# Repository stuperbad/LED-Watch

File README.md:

# LED-Watch

A round LED wristwatch: 132 small LEDs (12 hours, 60 minutes, 60 seconds as three concentric rings) driven straight from an AVR microcontroller, with an accelerometer to wake it. Two variants share the idea and some code but have different hardware, so each lives in its own folder.

| Open this KiCad project | Variant | Status |
|---|---|---|
| [`single-color/hardware/LED Watch - Single Color.kicad_pro`](single-color/hardware/) | White LEDs, solar-charged (TI BQ25570 + one Anysolar cell + two small LiPo cells), AVR128DB48, piezo buzzer, 42 mm board | **Revision A is an order candidate** (JLCPCB quote $308.63 for 5 assembled boards), fully routed, DRC clean, **not ordered yet**. Firmware (alarm, weekday lights, sounds) and a browser simulator are in the folder. Start with [`single-color/README.md`](single-color/README.md). Tagged `rev-A`. |
| [`rgb/LED Watch - RGB.kicad_pro`](rgb/) | RGB LEDs that JLCPCB can assemble (common-anode), AVR128DB64, solar + LiPo + buzzer like the single-colour watch | **Placement sketch only** (2026-10-15): board size and fit worked out, no schematic or routing yet. Start with `rgb/docs/DESIGN-SKETCH.md`. The earlier RGB board (Harvatek LEDs, ATmega165PA, fully routed, not buildable: parts out of stock) is in `rgb/archive/2026-10-14 old RGB board ...` |

## Layout of the repository
```
LED-Watch/
  single-color/        the solar white-LED watch
    hardware/          KiCad project, custom footprints, production files (Gerbers, BOM, placement), schematic generator
    firmware/          AVR firmware (C), browser simulator, tests
    docs/              design notes, decision log, checklists, datasheets, research
    tools/             layout / routing / checking scripts
    archive/           older board generations of this variant
  rgb/                 the RGB watch
    LED Watch - RGB.*  the RGB project (placement sketch, 2026-10-15)
    docs/              DESIGN-SKETCH.md, pin plan, BOM candidates
    footprints/ data/ tools/ renders/   LED footprint, LED map, sketch generator, pictures
    mechanical/        outline drawings and the 3D print (of the old 43 mm board)
    archive/           the old routed RGB board and everything older
```
Both variants live side by side on `main`; branches are for work in progress. Revisions are git tags (`rev-A`, ...) rather than file names.
Code that both variants will share (LED matrix scan, RTC and mode state machine, accelerometer driver) can move to a top-level `shared/` folder when RGB firmware starts; `single-color/firmware/` is the starting point.

## Reviewing
Open `single-color/README.md` (what everything is), then `single-color/docs/REVIEW-GUIDE.md` (what to check first), and `single-color/docs/PRE-ORDER-CHECKLIST.md` (what is still open).

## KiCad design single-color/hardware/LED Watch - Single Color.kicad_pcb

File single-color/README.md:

# LED Watch (single color, solar)

A wrist-worn clock that tells the time with 132 tiny white LEDs on three concentric rings (12 hour, 60 minute, 60 second), seven mode LEDs that double as weekday lights,
a piezo buzzer, a motion sensor to wake it, a solar cell and two LiPo cells on the back, and no case. Run by Evan Finkle with Claude (Anthropic) doing research, scripting and layout.

**Status (2026-11-02): revision C is the current design, not ordered yet.** Revision C is revision B with charging and programming moved from four pogo pads to a **USB-C receptacle** on the back (GCT USB4110, a TI BQ21040 charger, UPDI on the two SBU pins), the solar cell pad connection fixed (on revision B the cell pad was on a differently named net and not wired to the harvester), the outer LED-column arcs pulled in from the board edge, and the silkscreen reduced to the numbers, labels and a few orientation marks. Revision B (pogo pads, code word `pogo-b`) is deprecated and archived in `archive/boards/rev-B-pogo/`; revision A in `archive/boards/rev-A-2026-10-29-pre-repin/`. Nothing has been powered up.
Requires **KiCad 10** (the project files will not open in older versions).
The checklist of what is still open is `docs/PRE-ORDER-CHECKLIST.md`; the reasoning behind every decision is `docs/DECISION-LOG.md`.

| | |
|---|---|
| Board | 42.0 mm circle with two strap lugs and 2.5 mm strap slots, 4 layers, 1.6 mm, JLCPCB rules (0.10 mm track/space, 0.15 mm vias) |
| MCU | Microchip AVR128DB48 (VQFN-48), UPDI programming through the USB-C receptacle's SBU pins (1 k in series, BAT54WS clamp); no reset pad (RESET on PF6 is not wired out) |
| Power | Anysolar KXOB25-05X3TF cell -> TI BQ25570 harvester -> 2 protected LiPo pouches (JST SH plugs); USB-C 5 V -> TI BQ21040 charger (54 mA) -> the same pouches |
| Sensor / sound | ST LIS2DW12 accelerometer (wrist raise, tap), Murata PKMCS0909E4000-R1 piezo on PB4/PB5 |
| Buttons | two, symmetric, low on the face |

## Folder map

| Folder | What is in it |
|---|---|
| **`hardware/`** | **The KiCad project. Open `hardware/LED Watch - Single Color.kicad_pro`.** `LED Watch - Single Color.kicad_sch` (schematic, hand-arranged in KiCad since 2026-10-29; `gen_schematic.py` is only a reference now and would overwrite that layout), `LED Watch - Single Color.kicad_pcb` (the routed board), `footprints/LEDWatch.pretty` (custom footprints), `netlist.xml` (exported from the schematic, read by the firmware tools) |
| `hardware/production/` | what you send to JLCPCB (revision C): `LED Watch - Single Color - gerbers.zip` (+ the loose `gerbers/`), `assembly/BOM.csv` and `CPL.csv` |
| `hardware/source/` | inputs of the layout pipeline: `layout-D-hand-placement.kicad_pcb` (the hand placement the routing started from), `nets.txt`, `crystal_exclude.txt` |
| `hardware/renders/` | top and bottom pictures of the board |
| `hardware/REVISIONS.md` | the revision table (A and B archived, **C = current**); revisions are git tags, not file names |
| `firmware/` | the watch software: `c/` AVR firmware (portable core `watch.c`, hardware layer `hw/`), `sim/` browser simulator running the same logic, `HANDOFF.md` current status. Start with `firmware/HANDOFF.md` |
| `mechanical/` | 3D-printable strap/fit test models: blank board, board with big-part stand-ins, snap-on skin-side bumper (`print/` has the STL files, `README.md` the print notes, `make_models.py` rebuilds them) |
| `docs/` | `BRING-UP.md` (first power-up: how the battery and power work, measurements, programming), `DESIGN-UX.md` (modes, buttons, LEDs, sounds), `DECISION-LOG.md`, `PRE-ORDER-CHECKLIST.md`, `SCHEMATIC-GUIDE.md`, `JLCPCB-RULES.md`, `ASSEMBLY-AND-COST.md`, `mcu-pinmaps.md`, `PIN-VERIFICATION.md` (every MCU pin checked against the datasheets, run `tools/verify_pins.py`); `datasheets/`; `research/` (solar, power, MCU studies, the power workbook) |
| `tools/` | the scripts that produced and checked the layout (routing pipeline, DRC helpers, BOM/placement export). KiCad's own Python is needed for the `pcbnew` ones |
| `archive/` | older board generations and experiments (revision A, revision B with pogo pads); see `archive/README.md` |

## Regenerating things

```
# the netlist the firmware tools read (edit the schematic in KiCad; do not re-run gen_schematic.py over it)
cd hardware
"C:\Program Files\KiCad\10.0\bin\kicad-cli.exe" sch export netlist --format kicadxml -o netlist.xml "LED Watch - Single Color.kicad_sch"

# firmware pin map and simulator face data from the schematic netlist and the board
cd ..\firmware
python gen_pins.py
"C:\Program Files\KiCad\10.0\bin\python.exe" sim\export_face_board.py

# production files from the board
cd ..\hardware
kicad-cli pcb export gerbers --subtract-soldermask --layers F.Cu,In1.Cu,In2.Cu,B.Cu,F.Mask,B.Mask,F.Silkscreen,B.Silkscreen,Edge.Cuts -o production\gerbers\ "LED Watch - Single Color.kicad_pcb"
kicad-cli pcb export drill --format excellon --excellon-separate-th --generate-map --map-format gerberx2 -o production\gerbers\ "LED Watch - Single Color.kicad_pcb"
kicad-cli pcb export pos --format csv --units mm --side both --smd-only --exclude-dnp -o production\assembly\pos_raw.csv "LED Watch - Single Color.kicad_pcb"
python ..\tools\make_bom_cpl.py production\assembly\pos_raw.csv production\assembly
```

Firmware tests (PC): `python firmware\c\test\run_diff.py` (JavaScript vs C core, frame for frame), `run_unit.py`, `run_hw.py`. AVR build: `powershell -File firmware\c\build_fw.ps1`.
Simulator: `python firmware\sim\serve.py 8765`, then open http://127.0.0.1:8765/index.html.

## How the layout was made (so the tools make sense)
Evan hand-placed the parts in KiCad (`hardware/source/layout-D-hand-placement`), then Claude's scripts in `tools/` did the symmetry tidy-up, the real footprints, the crystal ground
guard, the polar routing of the LED rings (`polar_route.py`), a grid router for the rest (`grid_route2.py`), via/stub clean-up, the ground plane (`fix_gnd_zone.py`) and the checks
(`check_pad_entry.py`, `dfm_gaps.py`, DRC). Evan then hand-edited the result in KiCad. The step by step story is in `docs/DECISION-LOG.md`.

## Related
The earlier RGB version is in `../rgb/` (never built): open `../rgb/LED Watch - RGB.kicad_pro`.

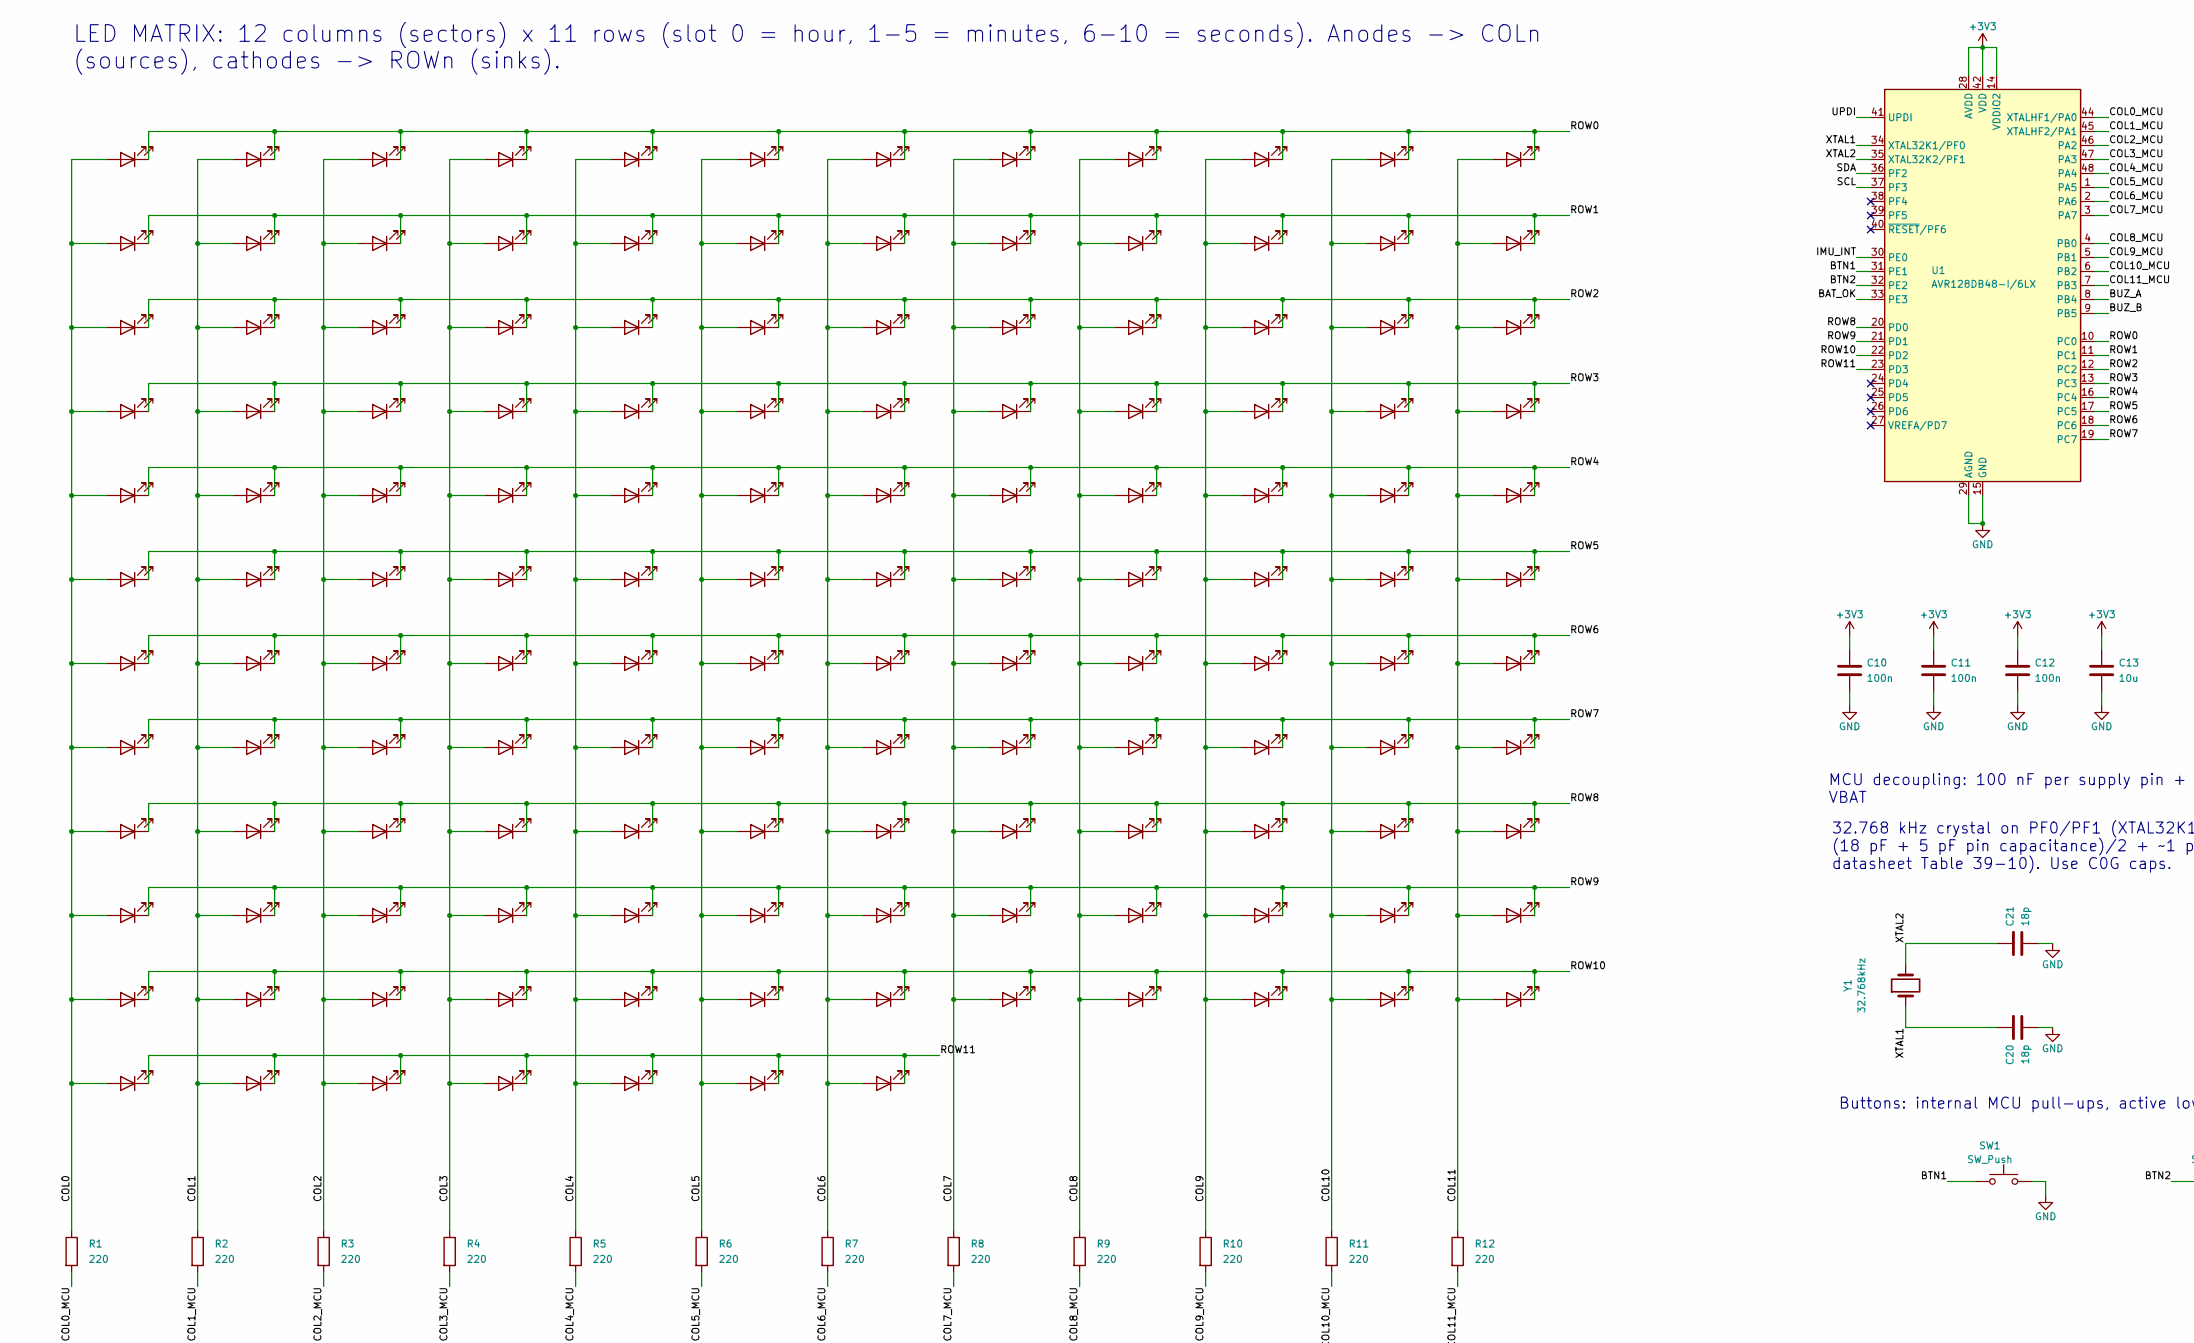
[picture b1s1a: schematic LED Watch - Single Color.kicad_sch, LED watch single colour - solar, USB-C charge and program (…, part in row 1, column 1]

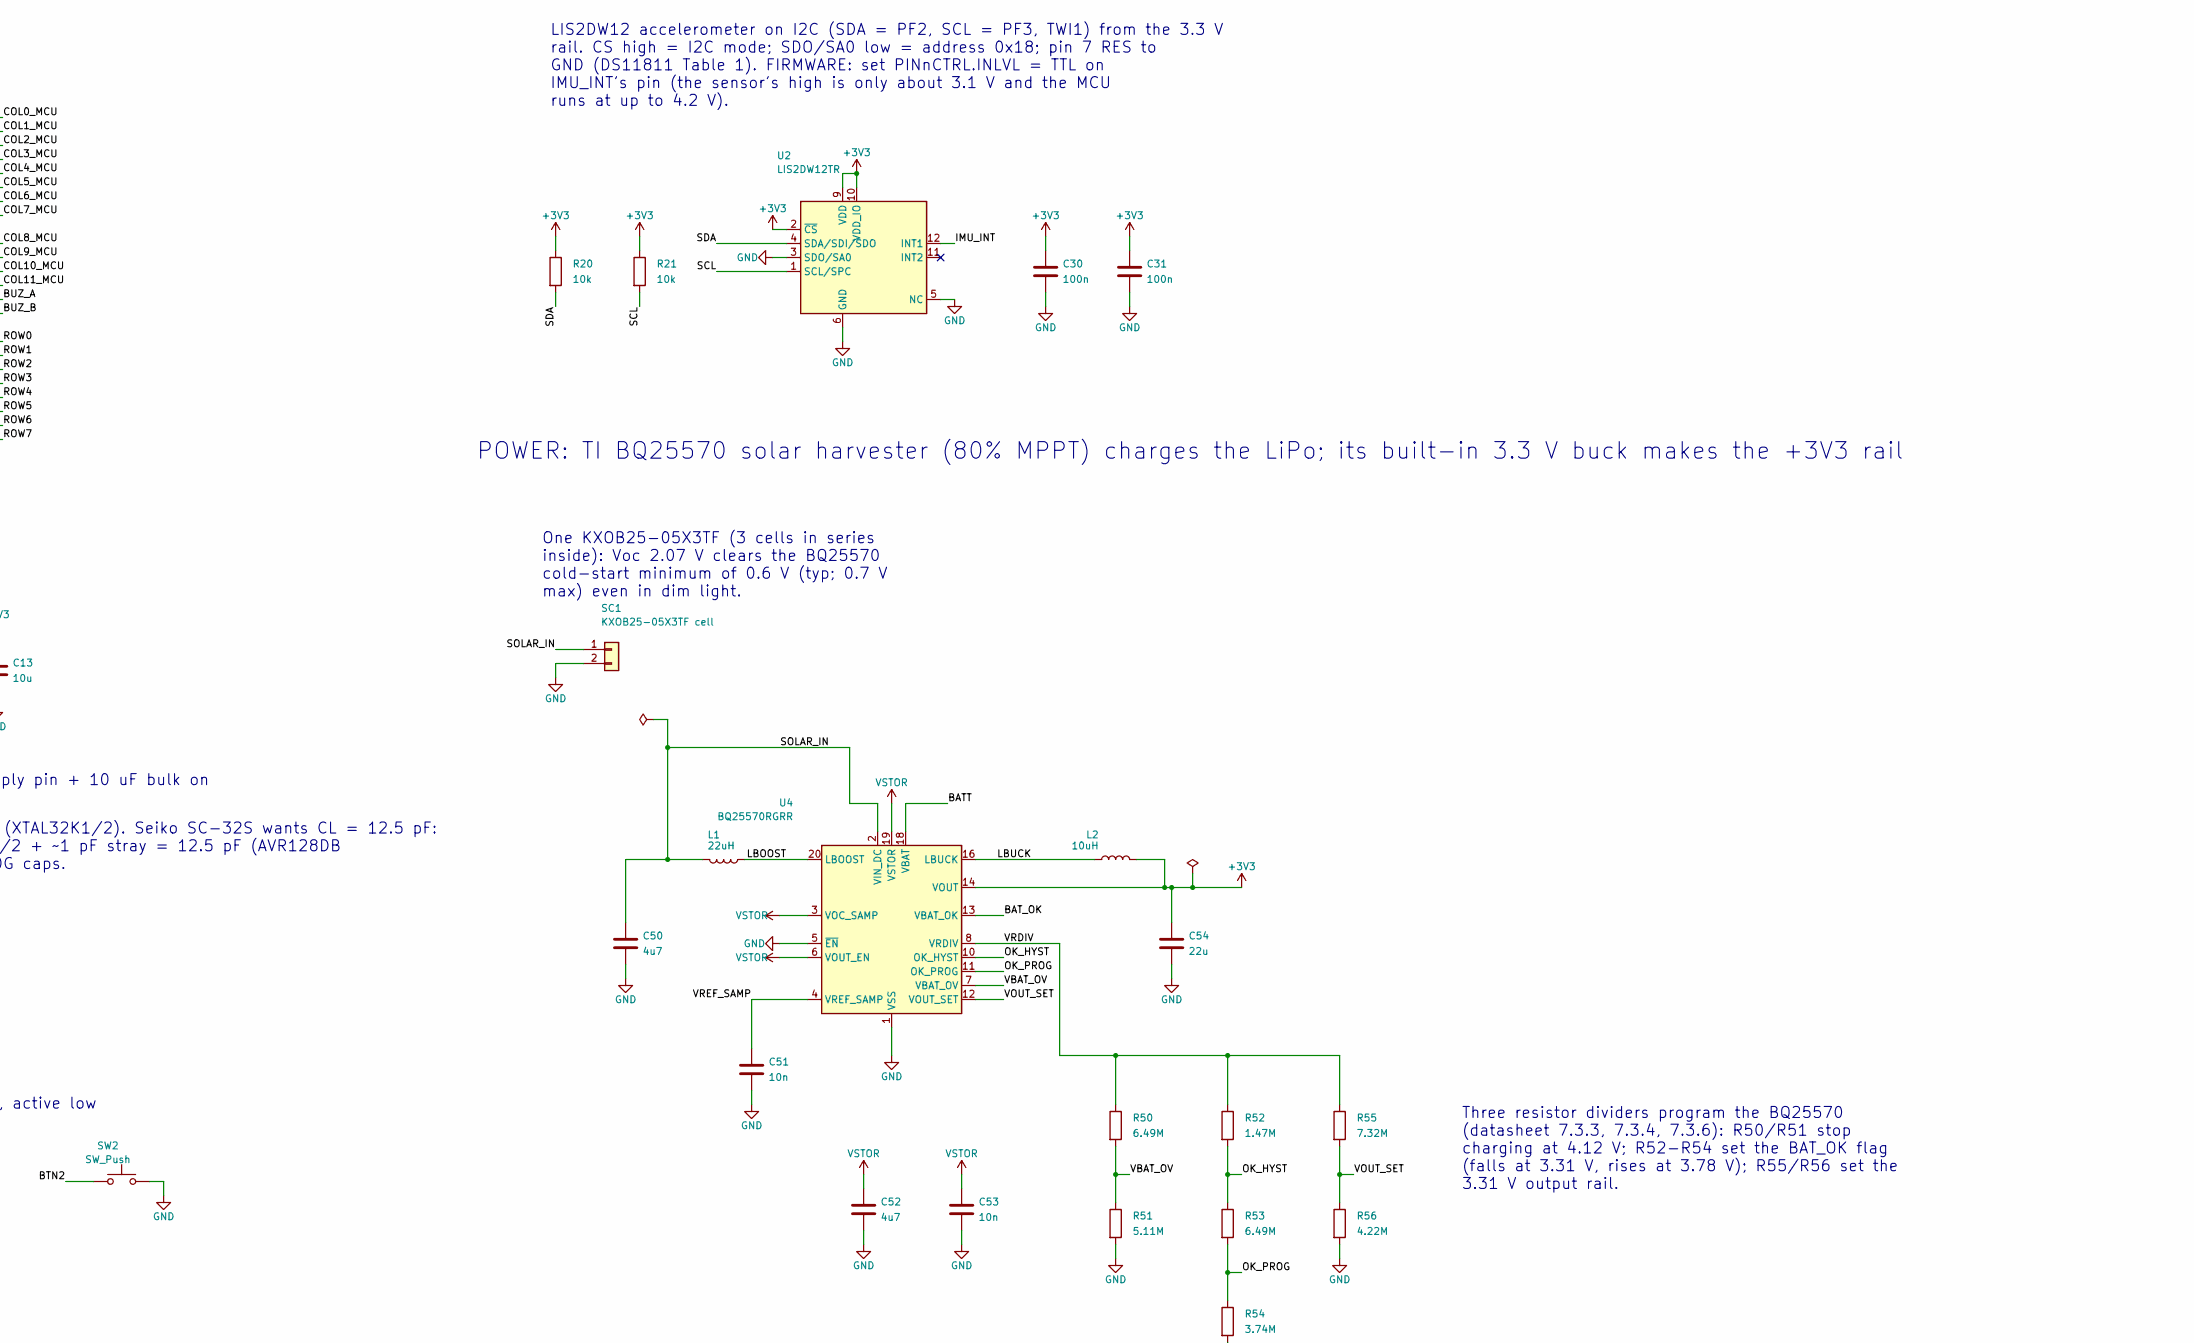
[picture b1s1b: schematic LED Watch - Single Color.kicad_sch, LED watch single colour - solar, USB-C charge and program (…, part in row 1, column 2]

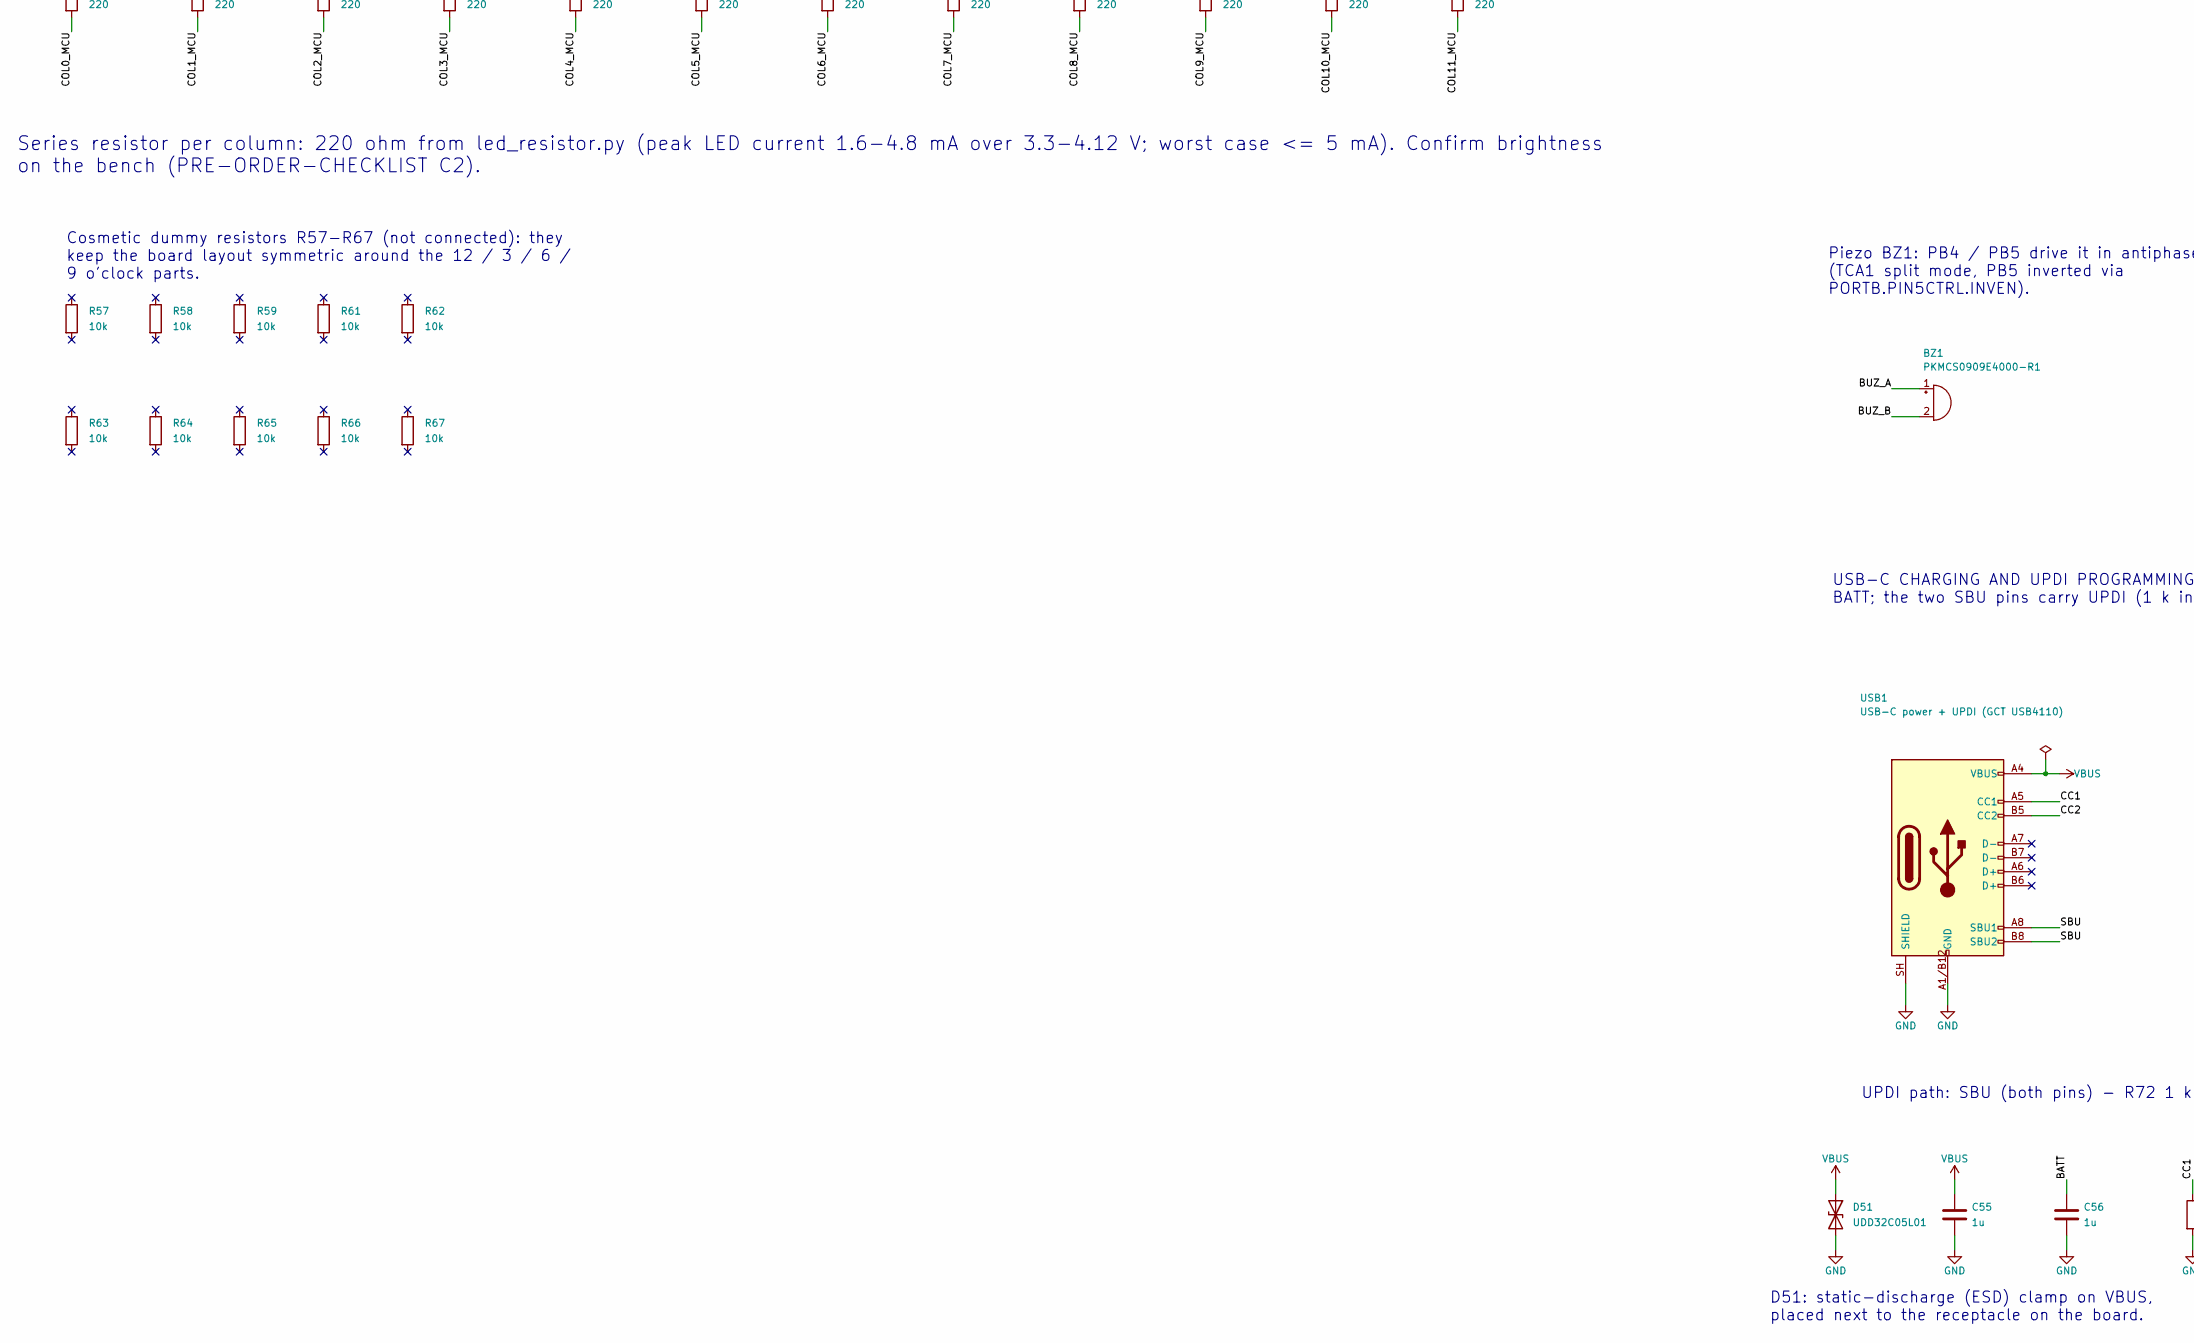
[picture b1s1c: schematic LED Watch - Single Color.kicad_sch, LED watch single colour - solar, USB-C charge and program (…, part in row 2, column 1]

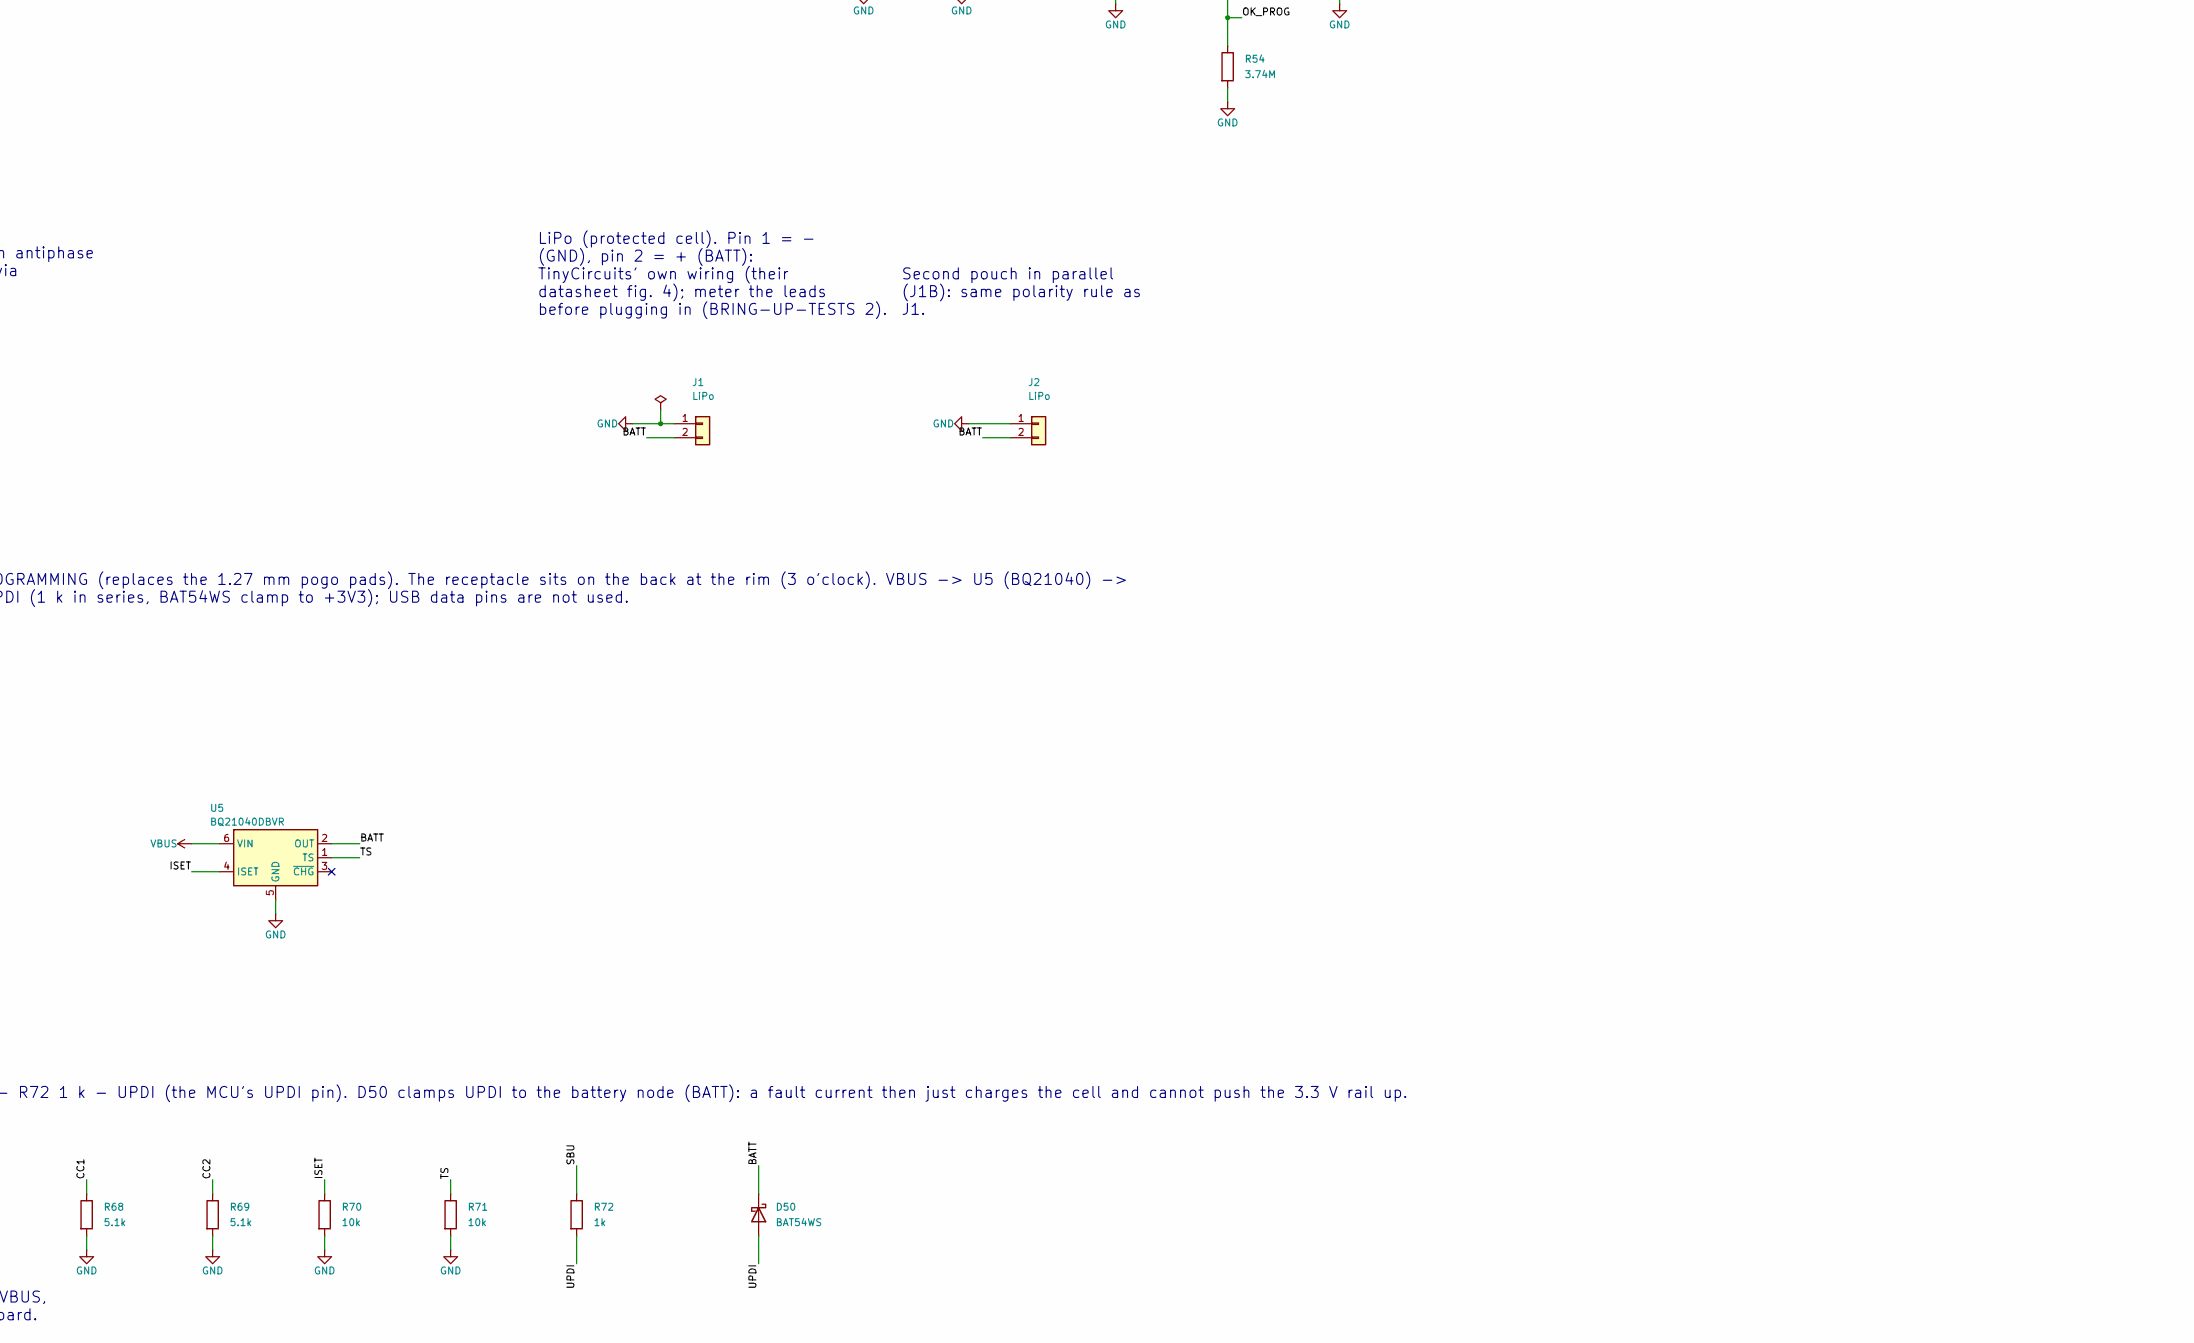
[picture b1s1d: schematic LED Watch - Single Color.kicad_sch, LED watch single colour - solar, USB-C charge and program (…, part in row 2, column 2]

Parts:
BZ1: PKMCS0909E4000-R1; Piezo_Murata_PKMCS0909E4000-R1_9x9mm; MPN PKMCS0909E4000-R1; LCSC C910763
C10, C11, C12, C30, C31: 100n; C_0402_1005Metric
C13: 10u; C_0402_1005Metric
C20, C21: 18p; C_0402_1005Metric
C50, C52: 4u7; C_0402_1005Metric
C51, C53: 10n; C_0402_1005Metric
C54: 22u; C_0805_2012Metric
C55, C56: 1u; C_0402_1005Metric; LCSC C52923
D50: BAT54WS; D_SOD-323; MPN BAT54WS; LCSC C304155
D51: UDD32C05L01; D_SOD-323; MPN UDD32C05L01; LCSC C19185929
H1, H2, H3, H4, H5, H6, H7, H8, H9, H10, H11, H12: LED white 0603; LED_0603_1608Metric
IND1: SET; LED_0402_1005Metric
IND2: TMR; LED_0402_1005Metric
IND3: BAT; LED_0402_1005Metric
IND4: FUN; LED_0402_1005Metric
IND5: CFG; LED_0402_1005Metric
IND6: LCK; LED_0402_1005Metric
IND7: ALM; LED_0402_1005Metric
J1, J2: LiPo; JST_SH_SM02B-SRSS-TB_1x02-1MP_P1.00mm_Horizontal
L1: 22uH; L_1210_3225Metric
L2: 10uH; L_1210_3225Metric
M0, M1, M2, M3, M4, M5, M6, M7, M8, M9, M10, M11, M12, M13, M14, M15, M16, M17, M18, M19, M20, M21, M22, M23, M24, M25, M26, M27, M28, M29, M30, M31, M32, M33, M34, M35, M36, M37, M38, M39, M40, M41, M42, M43, M44, M45, M46, M47, M48, M49, M50, M51, M52, M53, M54, M55, M56, M57, M58, M59: LED white 0402; LED_0402_1005Metric
R1, R2, R3, R4, R5, R6, R7, R8, R9, R10, R11, R12: 220; R_0402_1005Metric
R20, R21, R57, R58, R59, R61, R62, R63, R64, R65, R66, R67: 10k; R_0402_1005Metric
R50, R53: 6.49M; R_0402_1005Metric
R51: 5.11M; R_0402_1005Metric
R52: 1.47M; R_0402_1005Metric
R54: 3.74M; R_0402_1005Metric
R55: 7.32M; R_0402_1005Metric
R56: 4.22M; R_0402_1005Metric
R68, R69: 5.1k; R_0402_1005Metric; LCSC C25905
R70, R71: 10k; R_0402_1005Metric; LCSC C25744
R72: 1k; R_0402_1005Metric; LCSC C11702
S0, S1, S2, S3, S4, S5, S6, S7, S8, S9, S10, S11, S12, S13, S14, S15, S16, S17, S18, S19, S20, S21, S22, S23, S24, S25, S26, S27, S28, S29, S30, S31, S32, S33, S34, S35, S36, S37, S38, S39, S40, S41, S42, S43, S44, S45, S46, S47, S48, S49, S50, S51, S52, S53, S54, S55, S56, S57, S58, S59: LED white 0201; LED_0201_0603Metric
SC1: KXOB25-05X3TF cell; KXOB25_cell_2pad_23x8mm
SW1, SW2: SW_Push; SW_Push_1P1T_NO_CK_KMR2
U1: AVR128DB48-I/6LX; QFN-48-1EP_6x6mm_P0.4mm_EP4.2x4.2mm
U2: LIS2DW12TR; LGA-12_2x2mm_P0.5mm; MPN LIS2DW12TR
U4: BQ25570RGRR; BQ25570RGR_VQFN-20_3.5x3.5mm_P0.5mm_EP2.05mm
U5: BQ21040DBVR; SOT-23-6; MPN BQ21040DBVR; LCSC C202311
USB1: USB-C power + UPDI (GCT USB4110); USB_C_Receptacle_GCT_USB4110; MPN USB4110-GF-A
Y1: 32.768kHz; Crystal_SMD_3215-2Pin_3.2x1.5mm; MPN ABS07-32.768KHZ-T

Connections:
+3V3: C10.1, C11.1, C12.1, C13.1, C30.1, C31.1, C54.1, L2.2, R20.1, R21.1, U1.14 (VDDIO2), U1.28 (AVDD), U1.42 (VDD), U2.2 (~CS), U2.9 (VDD), U2.10 (VDD_IO), U4.14 (VOUT)
/BATT: C56.1, D50.1 (K), J1.2, J2.2, U4.18 (VBAT), U5.2 (OUT)
/BAT_OK: U1.33 (PE3), U4.13 (VBAT_OK)
/BTN1: SW1.1, U1.31 (PE1)
/BTN2: SW2.1, U1.32 (PE2)
/BUZ_A: BZ1.1 (+), U1.8 (PB4)
/BUZ_B: BZ1.2 (-), U1.9 (PB5)
/CC1: R68.1, USB1.A5 (CC1)
/CC2: R69.1, USB1.B5 (CC2)
/COL0: H12.2 (A), IND1.2 (A), M0.2 (A), M1.2 (A), M2.2 (A), M3.2 (A), M4.2 (A), R1.1, S0.2 (A), S1.2 (A), S2.2 (A), S3.2 (A), S4.2 (A)
/COL0_MCU: R1.2, U1.44 (XTALHF1/PA0)
/COL1: H1.2 (A), IND2.2 (A), M5.2 (A), M6.2 (A), M7.2 (A), M8.2 (A), M9.2 (A), R2.1, S5.2 (A), S6.2 (A), S7.2 (A), S8.2 (A), S9.2 (A)
/COL1_MCU: R2.2, U1.45 (XTALHF2/PA1)
/COL2: H2.2 (A), IND3.2 (A), M10.2 (A), M11.2 (A), M12.2 (A), M13.2 (A), M14.2 (A), R3.1, S10.2 (A), S11.2 (A), S12.2 (A), S13.2 (A), S14.2 (A)
/COL2_MCU: R3.2, U1.46 (PA2)
/COL3: H3.2 (A), IND4.2 (A), M15.2 (A), M16.2 (A), M17.2 (A), M18.2 (A), M19.2 (A), R4.1, S15.2 (A), S16.2 (A), S17.2 (A), S18.2 (A), S19.2 (A)
/COL3_MCU: R4.2, U1.47 (PA3)
/COL4: H4.2 (A), IND5.2 (A), M20.2 (A), M21.2 (A), M22.2 (A), M23.2 (A), M24.2 (A), R5.1, S20.2 (A), S21.2 (A), S22.2 (A), S23.2 (A), S24.2 (A)
/COL4_MCU: R5.2, U1.48 (PA4)
/COL5: H5.2 (A), IND6.2 (A), M25.2 (A), M26.2 (A), M27.2 (A), M28.2 (A), M29.2 (A), R6.1, S25.2 (A), S26.2 (A), S27.2 (A), S28.2 (A), S29.2 (A)
/COL5_MCU: R6.2, U1.1 (PA5)
/COL6: H6.2 (A), IND7.2 (A), M30.2 (A), M31.2 (A), M32.2 (A), M33.2 (A), M34.2 (A), R7.1, S30.2 (A), S31.2 (A), S32.2 (A), S33.2 (A), S34.2 (A)
/COL6_MCU: R7.2, U1.2 (PA6)
/COL7: H7.2 (A), M35.2 (A), M36.2 (A), M37.2 (A), M38.2 (A), M39.2 (A), R8.1, S35.2 (A), S36.2 (A), S37.2 (A), S38.2 (A), S39.2 (A)
/COL7_MCU: R8.2, U1.3 (PA7)
/COL8: H8.2 (A), M40.2 (A), M41.2 (A), M42.2 (A), M43.2 (A), M44.2 (A), R9.1, S40.2 (A), S41.2 (A), S42.2 (A), S43.2 (A), S44.2 (A)
/COL8_MCU: R9.2, U1.4 (PB0)
/COL9: H9.2 (A), M45.2 (A), M46.2 (A), M47.2 (A), M48.2 (A), M49.2 (A), R10.1, S45.2 (A), S46.2 (A), S47.2 (A), S48.2 (A), S49.2 (A)
/COL9_MCU: R10.2, U1.5 (PB1)
/COL10: H10.2 (A), M50.2 (A), M51.2 (A), M52.2 (A), M53.2 (A), M54.2 (A), R11.1, S50.2 (A), S51.2 (A), S52.2 (A), S53.2 (A), S54.2 (A)
/COL10_MCU: R11.2, U1.6 (PB2)
/COL11: H11.2 (A), M55.2 (A), M56.2 (A), M57.2 (A), M58.2 (A), M59.2 (A), R12.1, S55.2 (A), S56.2 (A), S57.2 (A), S58.2 (A), S59.2 (A)
/COL11_MCU: R12.2, U1.7 (PB3)
/IMU_INT: U1.30 (PE0), U2.12 (INT1)
/ISET: R70.1, U5.4 (ISET)
/LBOOST: L1.1, U4.20 (LBOOST)
/LBUCK: L2.1, U4.16 (LBUCK)
/OK_HYST: R52.2, R53.1, U4.10 (OK_HYST)
/OK_PROG: R53.2, R54.1, U4.11 (OK_PROG)
/ROW0: H1.1 (K), H2.1 (K), H3.1 (K), H4.1 (K), H5.1 (K), H6.1 (K), H7.1 (K), H8.1 (K), H9.1 (K), H10.1 (K), H11.1 (K), H12.1 (K), U1.10 (PC0)
/ROW1: M0.1 (K), M5.1 (K), M10.1 (K), M15.1 (K), M20.1 (K), M25.1 (K), M30.1 (K), M35.1 (K), M40.1 (K), M45.1 (K), M50.1 (K), M55.1 (K), U1.11 (PC1)
/ROW2: M1.1 (K), M6.1 (K), M11.1 (K), M16.1 (K), M21.1 (K), M26.1 (K), M31.1 (K), M36.1 (K), M41.1 (K), M46.1 (K), M51.1 (K), M56.1 (K), U1.12 (PC2)
/ROW3: M2.1 (K), M7.1 (K), M12.1 (K), M17.1 (K), M22.1 (K), M27.1 (K), M32.1 (K), M37.1 (K), M42.1 (K), M47.1 (K), M52.1 (K), M57.1 (K), U1.13 (PC3)
/ROW4: M3.1 (K), M8.1 (K), M13.1 (K), M18.1 (K), M23.1 (K), M28.1 (K), M33.1 (K), M38.1 (K), M43.1 (K), M48.1 (K), M53.1 (K), M58.1 (K), U1.16 (PC4)
/ROW5: M4.1 (K), M9.1 (K), M14.1 (K), M19.1 (K), M24.1 (K), M29.1 (K), M34.1 (K), M39.1 (K), M44.1 (K), M49.1 (K), M54.1 (K), M59.1 (K), U1.17 (PC5)
/ROW6: S0.1 (K), S5.1 (K), S10.1 (K), S15.1 (K), S20.1 (K), S25.1 (K), S30.1 (K), S35.1 (K), S40.1 (K), S45.1 (K), S50.1 (K), S55.1 (K), U1.18 (PC6)
/ROW7: S1.1 (K), S6.1 (K), S11.1 (K), S16.1 (K), S21.1 (K), S26.1 (K), S31.1 (K), S36.1 (K), S41.1 (K), S46.1 (K), S51.1 (K), S56.1 (K), U1.19 (PC7)
/ROW8: S2.1 (K), S7.1 (K), S12.1 (K), S17.1 (K), S22.1 (K), S27.1 (K), S32.1 (K), S37.1 (K), S42.1 (K), S47.1 (K), S52.1 (K), S57.1 (K), U1.20 (PD0)
/ROW9: S3.1 (K), S8.1 (K), S13.1 (K), S18.1 (K), S23.1 (K), S28.1 (K), S33.1 (K), S38.1 (K), S43.1 (K), S48.1 (K), S53.1 (K), S58.1 (K), U1.21 (PD1)
/ROW10: S4.1 (K), S9.1 (K), S14.1 (K), S19.1 (K), S24.1 (K), S29.1 (K), S34.1 (K), S39.1 (K), S44.1 (K), S49.1 (K), S54.1 (K), S59.1 (K), U1.22 (PD2)
/ROW11: IND1.1 (K), IND2.1 (K), IND3.1 (K), IND4.1 (K), IND5.1 (K), IND6.1 (K), IND7.1 (K), U1.23 (PD3)
/SBU: R72.1, USB1.A8 (SBU1), USB1.B8 (SBU2)
/SCL: R21.2, U1.37 (PF3), U2.1 (SCL/SPC)
/SDA: R20.2, U1.36 (PF2), U2.4 (SDA/SDI/SDO)
/SOLAR_IN: C50.1, L1.2, SC1.1, U4.2 (VIN_DC)
/TS: R71.1, U5.1 (TS)
/UPDI: D50.2 (A), R72.2, U1.41 (UPDI)
/VBAT_OV: R50.2, R51.1, U4.7 (VBAT_OV)
/VOUT_SET: R55.2, R56.1, U4.12 (VOUT_SET)
/VRDIV: R50.1, R52.1, R55.1, U4.8 (VRDIV)
/VREF_SAMP: C51.1, U4.4 (VREF_SAMP)
/XTAL1: C20.1, U1.34 (XTAL32K1/PF0), Y1.1
/XTAL2: C21.1, U1.35 (XTAL32K2/PF1), Y1.2
GND: C10.2, C11.2, C12.2, C13.2, C20.2, C21.2, C30.2, C31.2, C50.2, C51.2, C52.2, C53.2, C54.2, C55.2, C56.2, D51.2 (A2), J1.1, J2.1, R51.2, R54.2, R56.2, R68.2, R69.2, R70.2, R71.2, SC1.2, SW1.2, SW2.2, U1.15 (GND), U1.29 (AGND), U1.43 (GND), U1.49 (GND), U2.3 (SDO/SA0), U2.5 (NC), U2.6 (GND), U2.7 (RES), U2.8 (GND), U4.1 (VSS), U4.5 (~EN), U4.9 (VSS), U4.15 (VSS), U4.17 (VSS), U4.21 (VSS), U5.5 (GND), USB1.A1 (GND), USB1.A1/B12 (GND), USB1.A12 (GND), USB1.A12/B1 (GND), USB1.B1 (GND), USB1.B12 (GND), USB1.SH (SHIELD)
VBUS: C55.1, D51.1 (A1), U5.6 (VIN), USB1.A4 (VBUS), USB1.A9 (VBUS), USB1.B4 (VBUS), USB1.B9 (VBUS)
VSTOR: C52.1, C53.1, U4.3 (VOC_SAMP), U4.6 (VOUT_EN), U4.19 (VSTOR)

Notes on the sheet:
LiPo (protected cell). Pin 1 = - (GND), pin 2 = + (BATT): TinyCircuits' own wiring (their datasheet fig. 4); meter the leads before plugging in (BRING-UP-TESTS 2).
UPDI path: SBU (both pins) - R72 1 k - UPDI (the MCU's UPDI pin). D50 clamps UPDI to the battery node (BATT): a fault current then just charges the cell and cannot push the 3.3 V rail up.
MCU decoupling: 100 nF per supply pin + 10 uF bulk on VBAT
LED MATRIX: 12 columns (sectors) x 11 rows (slot 0 = hour, 1-5 = minutes, 6-10 = seconds). Anodes -> COLn (sources), cathodes -> ROWn (sinks).
POWER: TI BQ25570 solar harvester (80% MPPT) charges the LiPo; its built-in 3.3 V buck makes the +3V3 rail
LIS2DW12 accelerometer on I2C (SDA = PF2, SCL = PF3, TWI1) from the 3.3 V rail. CS high = I2C mode; SDO/SA0 low = address 0x18; pin 7 RES to GND (DS11811 Table 1). FIRMWARE: set PINnCTRL.INLVL = TTL on IMU_INT's pin (the sensor's high is only about 3.1 V and the MCU runs at up to 4.2 V).
Second pouch in parallel (J1B): same polarity rule as J1.
Series resistor per column: 220 ohm from led_resistor.py (peak LED current 1.6-4.8 mA over 3.3-4.12 V; worst case <= 5 mA). Confirm brightness on the bench (PRE-ORDER-CHECKLIST C2).
Piezo BZ1: PB4 / PB5 drive it in antiphase (TCA1 split mode, PB5 inverted via PORTB.PIN5CTRL.INVEN).
Three resistor dividers program the BQ25570 (datasheet 7.3.3, 7.3.4, 7.3.6): R50/R51 stop charging at 4.12 V; R52-R54 set the BAT_OK flag (falls at 3.31 V, rises at 3.78 V); R55/R56 set the 3.31 V output rail.
Cosmetic dummy resistors R57-R67 (not connected): they keep the board layout symmetric around the 12 / 3 / 6 / 9 o'clock parts.
USB-C CHARGING AND UPDI PROGRAMMING (replaces the 1.27 mm pogo pads). The receptacle sits on the back at the rim (3 o'clock). VBUS -> U5 (BQ21040) -> BATT; the two SBU pins carry UPDI (1 k in series, BAT54WS clamp to +3V3); USB data pins are not used.
One KXOB25-05X3TF (3 cells in series inside): Voc 2.07 V clears the BQ25570 cold-start minimum of 0.6 V (typ; 0.7 V max) even in dim light.
Buttons: internal MCU pull-ups, active low
D51: static-discharge (ESD) clamp on VBUS, placed next to the receptacle on the board.
32.768 kHz crystal on PF0/PF1 (XTAL32K1/2). Seiko SC-32S wants CL = 12.5 pF: (18 pF + 5 pF pin capacitance)/2 + ~1 pF stray = 12.5 pF (AVR128DB datasheet Table 39-10). Use C0G caps.
